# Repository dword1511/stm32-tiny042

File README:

This project contains a minimalist USB board for STM32F042F6P6. It has PA0-PA7
pins broken out and a LED connected to PA14, and can serve as a highly compact
development board.

My version of the board uses a LP5907 LDO. Other LDOs in SOT23-5 packages
should also work, but you may need to cut the "bypass" pin of your LDO. (LP5907
does not have a bypass pin, so it is grounded.)

The project also contains a blinky example, which may be used as a foundation
for other projects. To build, simply type "make", or read the header of the
Makefile for details. To flash, connect BOOT0 ("BT0") to 3.3V ("3V3") on the
board, plug the board into a USB slot, then type "make flash". Depending system
configuration, you may need to use sudo. See

  http://www.libopencm3.org/wiki/USB_DFU

for details. Having a udev rule in place is highly recommended so you do not
have to run make with root privilege.

Order link on OSH Park:

  https://oshpark.com/shared_projects/WYQE2OGu

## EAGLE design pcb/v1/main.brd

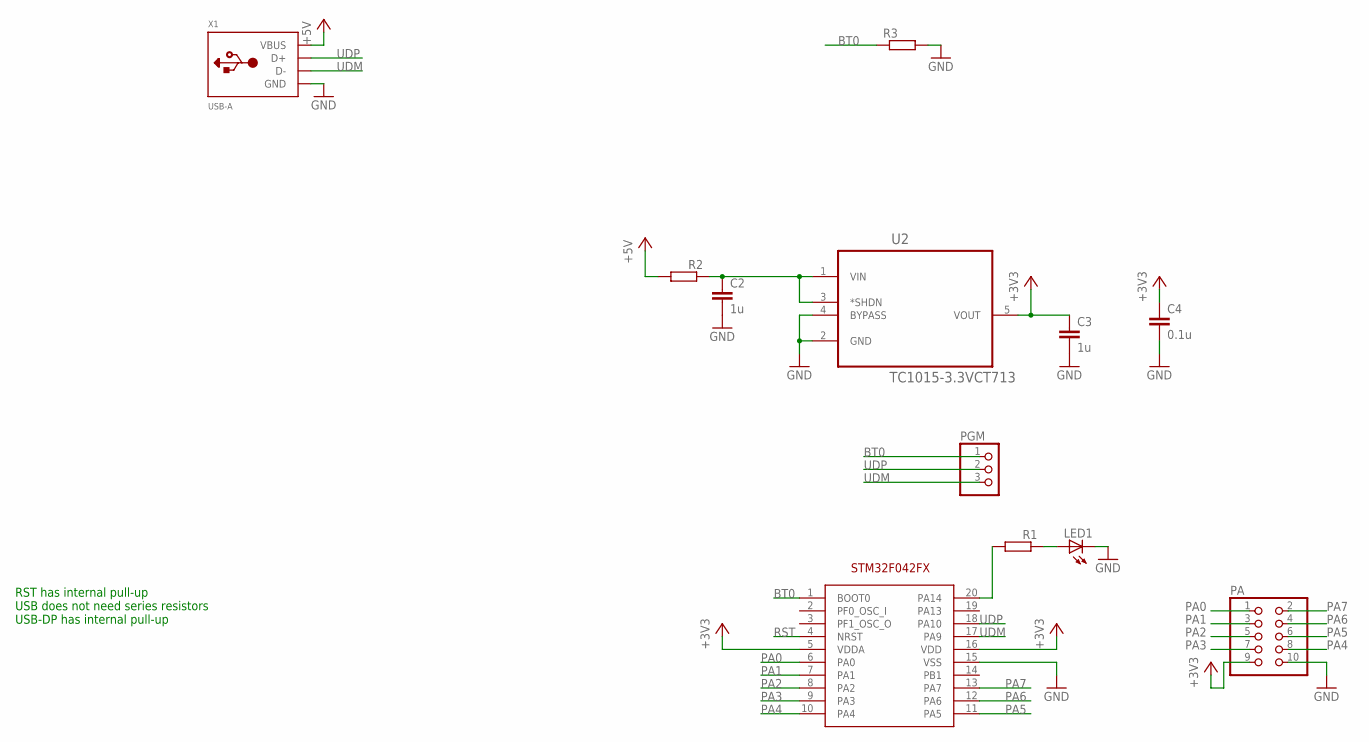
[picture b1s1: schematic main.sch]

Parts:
C2, C3: 1u; C0805K
C4: 0.1u; C0805K
LED1: LEDCHIPLED_0805; CHIPLED_0805
PA: PINHD-2X5; 2X05
PGM: PINHD-1X3; 1X03
R1, R2, R3: R-EU_R0805; R0805
U1: STM32F042FX; TSSOP20
U2: TC1015-3.3VCT713; SOT95P270X145-5N
X1: USB-A; MOLEX_480371000

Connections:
+3V3: C3.1, C4.1, PA.9, U1.5 (VDDA), U1.16 (VDD), U2.5 (VOUT)
+5V: R2.2, X1.1 (VBUS)
BT0: PGM.1, R3.1, U1.1 (BOOT0)
GND: C2.2, C3.2, C4.2, LED1.C, PA.10, R3.2, U1.15 (VSS), U2.2 (GND), U2.4 (BYPASS), X1.4 (GND)
unnamed: R1.2, U1.20 (PA14)
unnamed: LED1.A, R1.1
unnamed: C2.1, R2.1, U2.1 (VIN), U2.3 (*SHDN)
PA0: PA.1, U1.6 (PA0)
PA1: PA.3, U1.7 (PA1)
PA2: PA.5, U1.8 (PA2)
PA3: PA.7, U1.9 (PA3)
PA4: PA.8, U1.10 (PA4)
PA5: PA.6, U1.11 (PA5)
PA6: PA.4, U1.12 (PA6)
PA7: PA.2, U1.13 (PA7)
RST: U1.4 (NRST)
UDM: PGM.3, U1.17 (PA9), X1.2 (D-)
UDP: PGM.2, U1.18 (PA10), X1.3 (D+)

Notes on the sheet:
RST has internal pull-up USB does not need series resistors USB-DP has internal pull-up

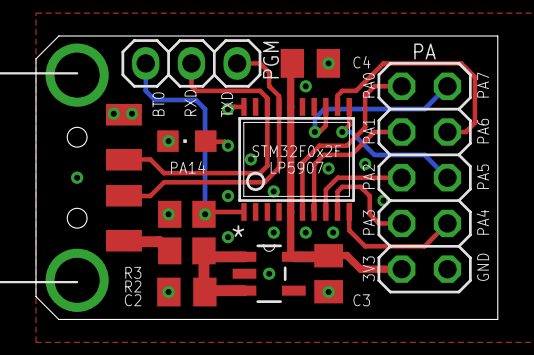
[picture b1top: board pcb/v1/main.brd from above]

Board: 2 copper layers, 25.7 x 15.7 mm, 12 parts (1 on the bottom side), 17 nets.

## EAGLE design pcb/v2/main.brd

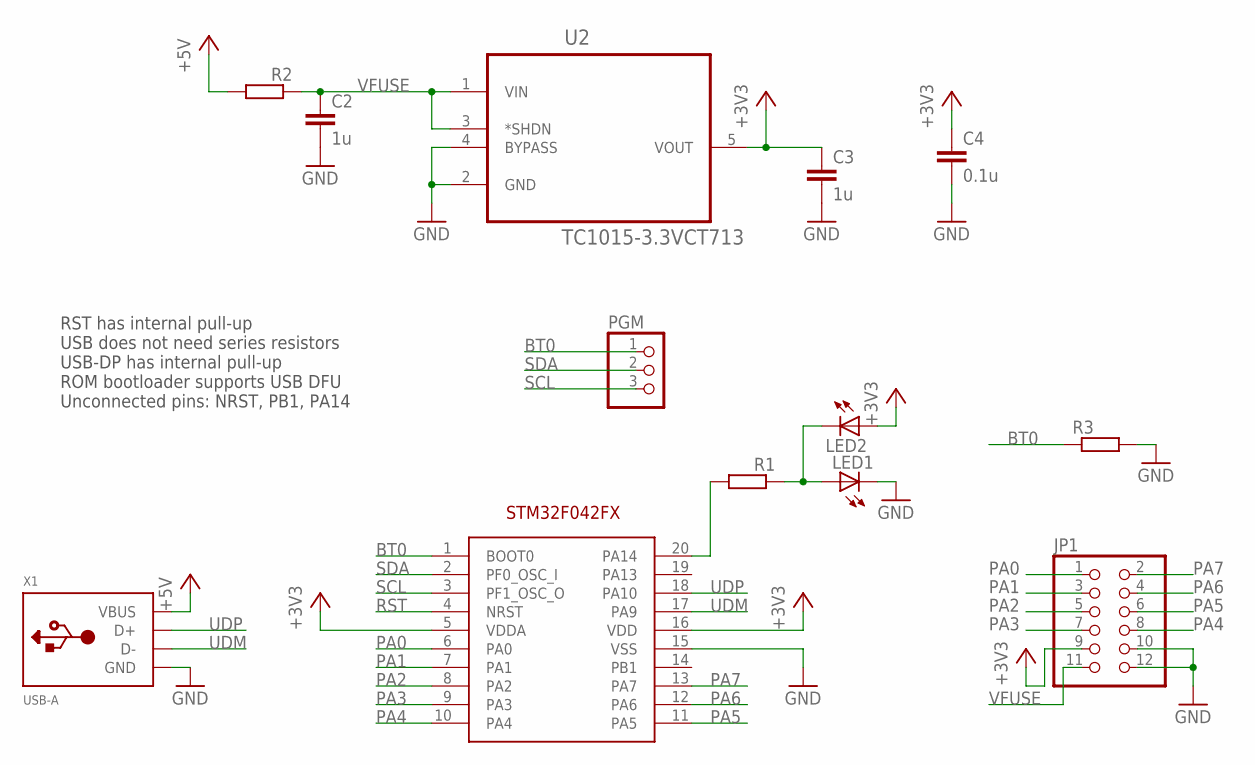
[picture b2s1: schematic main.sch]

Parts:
C2, C3: 1u; C0805K
C4: 0.1u; C0805K
JP1: PINHD-2X6; 2X06
LED1, LED2: LEDCHIPLED_0805; CHIPLED_0805
PGM: PINHD-1X3; 1X03
R1, R2, R3: R-EU_R0805; R0805
U1: STM32F042FX; TSSOP20
U2: TC1015-3.3VCT713; SOT95P270X145-5N
X1: USB-A; MOLEX_480371000

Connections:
+3V3: C3.1, C4.1, JP1.9, LED2.A, U1.5 (VDDA), U1.16 (VDD), U2.5 (VOUT)
+5V: R2.2, X1.1 (VBUS)
BT0: PGM.1, R3.1, U1.1 (BOOT0)
GND: C2.2, C3.2, C4.2, JP1.10, JP1.12, LED1.C, R3.2, U1.15 (VSS), U2.2 (GND), U2.4 (BYPASS), X1.4 (GND)
unnamed: R1.2, U1.20 (PA14)
unnamed: LED1.A, LED2.C, R1.1
PA0: JP1.1, U1.6 (PA0)
PA1: JP1.3, U1.7 (PA1)
PA2: JP1.5, U1.8 (PA2)
PA3: JP1.7, U1.9 (PA3)
PA4: JP1.8, U1.10 (PA4)
PA5: JP1.6, U1.11 (PA5)
PA6: JP1.4, U1.12 (PA6)
PA7: JP1.2, U1.13 (PA7)
RST: U1.4 (NRST)
SCL: PGM.3, U1.3 (PF1_OSC_O)
SDA: PGM.2, U1.2 (PF0_OSC_I)
UDM: U1.17 (PA9), X1.2 (D-)
UDP: U1.18 (PA10), X1.3 (D+)
VFUSE: C2.1, JP1.11, R2.1, U2.1 (VIN), U2.3 (*SHDN)

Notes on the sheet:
RST has internal pull-up USB does not need series resistors USB-DP has internal pull-up ROM bootloader supports USB DFU Unconnected pins: NRST, PB1, PA14

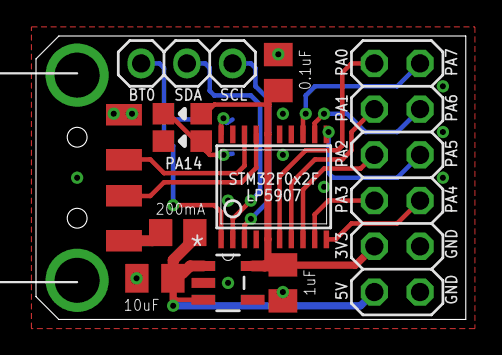
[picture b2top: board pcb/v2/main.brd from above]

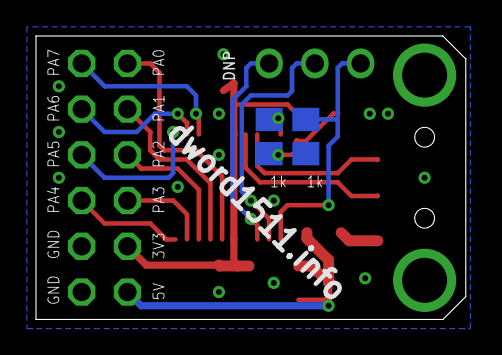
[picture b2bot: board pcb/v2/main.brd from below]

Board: 2 copper layers, 23.9 x 15.7 mm, 13 parts (2 on the bottom side), 19 nets.

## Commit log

2016-01-27 init commit
2016-01-27 verified everything works.
2016-01-27 added OSH Park link
2016-01-30 remove leftovers in makefile
2016-03-03 new version of board added
